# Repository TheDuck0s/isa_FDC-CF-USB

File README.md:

# ISA FDC, XT-CF, USB Card

This is an IBM XT-compatible FDC, XT-CF-Lite and USB card, based on a design (FDC & XT-CF-Lite-V4) by [Sergey Kiselev](https://github.com/skiselev).

# The Idea

The goal of this project is to create an XT-compatible computer on a passive backplane with a modular card-based architecture, minimizing the overall footprint while providing support for all common expansion cards.

# Hardware Documentation
Schematic PDF:
[Schematic - Version 1.0](isa_FDC-CF-USB_Schematic.pdf)

PCB PDF:
[Board Design - Version 1.0](isa_FDC-CF-USB_Board_Design.pdf)

Gerber Files:
[Gerber- Version 1.0](gerber/)

# Bill of Materials
    
coming soon...

# Release Notes

### Changes:

#### Version 1.0

 * Initial Release

 # Benchmarks

### Checkit 3.0 Benchmark:

#### @9.55 MHz
 * XT-CF: 725KB/s

# Final Note
 * The card is tested and works.
 * This card won't fit Sergey's case ([this one](https://github.com/skiselev/micro_8088_case)). The case will need to be enlarged.
 * Card size 185.3 mm x 102.9 mm

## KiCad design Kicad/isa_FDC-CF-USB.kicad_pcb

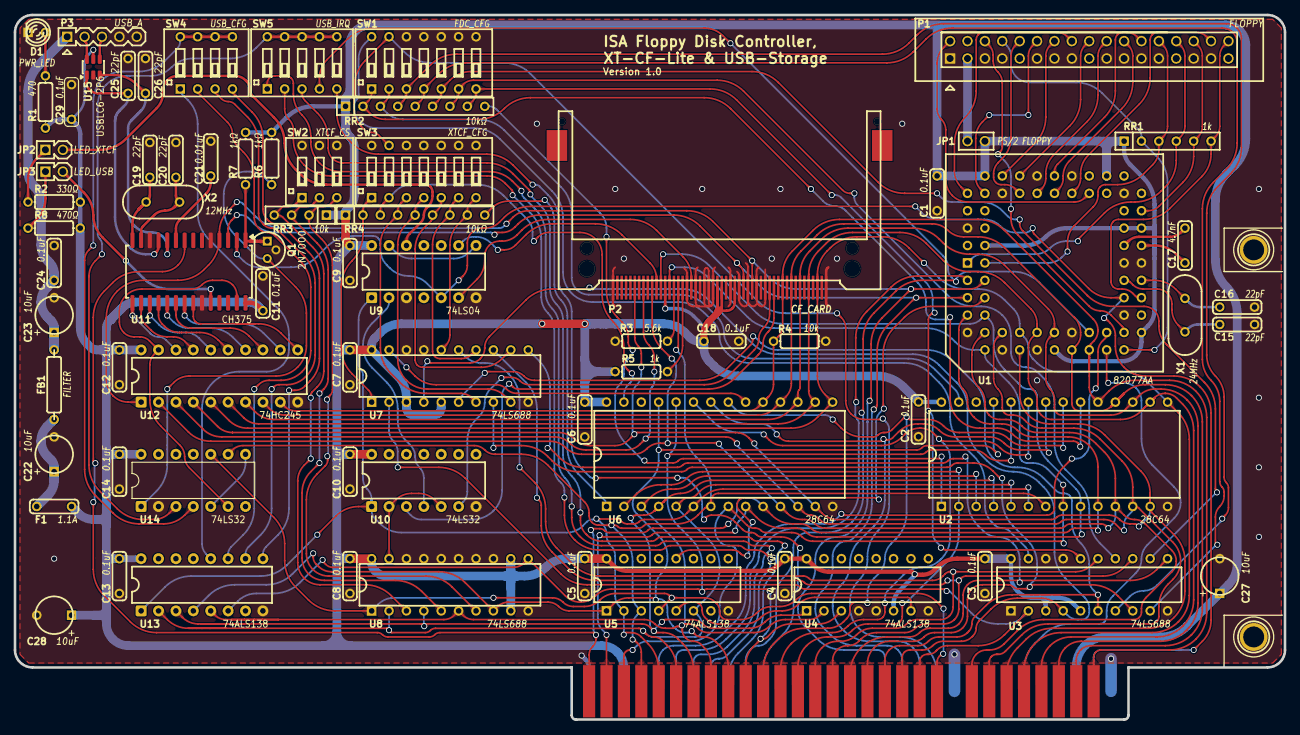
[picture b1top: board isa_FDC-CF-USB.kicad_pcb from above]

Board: 2 copper layers, 185.4 x 102.9 mm, 76 parts (0 on the bottom side), 130 nets.

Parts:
BUS1: PCB Edge Connector; Conn_Bus_ISA8
C1, C6, C7, C8, C9, C10, C11, C12, C13, C14, C18, C24, C29: 0.1uF; Cap_Cer_508
C2, C3, C4, C5: 0.1uF; Cap_Cer_504
C15, C16: 22pF; Cap_Cer_504
C17: 4.7nF; Cap_Cer_504
C19, C20, C25, C26: 22pF; Cap_Cer_508
C21: 0.01uF; Cap_Cer_508
C22, C23, C27, C28: 10uF; Cap_Tant_508
D1: PWR_LED; LED_3mm
F1: 1.1A; Cap_Cer_508
FB1: FILTER; Res_1016
HOLE1, HOLE2: CONN_1; HOLE_3MM
JP1: PS/2 FLOPPY; Conn_Pin_Header_2x1_Nokey
JP2: LED_XTCF; Conn_Pin_Header_2x1_2.54mm
JP3: LED_USB; Conn_Pin_Header_2x1_2.54mm
P1: FLOPPY; Conn_Pin_Header_17x2_2.54mm_Shrouded
P2: CF_CARD; Conn_CF_N7E50-Q516XX-40
P3: USB_A; Conn_Pin_Header_5x1_2.54mm
Q1: 2N7000; TO-92
R1: 470; Res_762
R2: 330Ω; Res_762
R3: 5.6k; Res_762
R4: 10k; Res_762
R5: 1k; Res_762
R6, R7: 1kΩ; Res_762
R8: 470Ω; Res_762
RR1: 1k; Conn_SIL6
RR2, RR4: 10kΩ; Conn_SIL9
RR3: 10k; Conn_SIL5
SW1: FDC_CFG; Switch_DIP_7_Positions
SW2: XTCF_CS; Switch_DIP_3_Positions
SW3: XTCF_CFG; Switch_DIP_7_Positions
SW4: USB_CFG; Switch_DIP_4_Positions
SW5: USB_IRQ; Switch_DIP_5_Positions
U1: 82077AA; PLCC68_TH
U2: 28C64; DIP28_600
U3: 74LS688; DIP20_300
U4, U5: 74ALS138; DIP16_300
U6: 28C64; IC_DIP28_600
U7, U8: 74LS688; IC_DIP20_300
U9: 74LS04; DIP-14_W7.62mm
U10, U14: 74LS32; DIP-14_W7.62mm
U11: CH375; SOP-28_8.4x18.16mm_P1.27mm
U12: 74HC245; DIP-20_W7.62mm
U13: 74ALS138; DIP-16_W7.62mm
U15: USBLC6-2P6; SOT-23-6
X1: 24MHz; Crystal_HC-49U_Vert
X2: 12MHz; Crystal_HC-49U_Vert

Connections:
/A0: BUS1.62 (SA0), U1.7 (A0), U2.10 (A0), U6.10 (A0), U11.8 (A0)
/A1: BUS1.61 (SA1), P2.20 (A0), U1.8 (A1), U2.9 (A1), U6.9 (A1)
/A2: BUS1.60 (SA2), P2.19 (A1), U1.10 (A2), U2.8 (A2), U6.8 (A2)
/A3: BUS1.59 (SA3), P2.18 (A2), U2.7 (A3), U5.3 (C), U6.7 (A3), U14.9
/A4: BUS1.58 (SA4), U2.6 (A4), U5.2 (B), U6.6 (A4), U9.1, U10.1, U13.1 (A)
/A5: BUS1.57 (SA5), U2.5 (A5), U5.6 (G1), U6.5 (A5), U8.2 (P0), U13.2 (B)
/A6: BUS1.56 (SA6), U2.4 (A6), U4.1 (A), U6.4 (A6), U8.4 (P1), U13.3 (C)
/A7: BUS1.55 (SA7), U2.3 (A7), U4.2 (B), U6.3 (A7), U8.6 (P2), U13.5 (~G2B)
/A8: BUS1.54 (SA8), U2.25 (A8), U5.1 (A), U6.25 (A8), U8.8 (P3), U13.4 (~G2A)
/A9: BUS1.53 (SA9), U2.24 (A9), U4.3 (C), U6.24 (A9), U8.11 (P4), U13.6 (G1)
/A10: BUS1.52 (SA10), U2.21 (A10), U6.21 (A10)
/A11: BUS1.51 (SA11), U2.23 (A11), U6.23 (A11)
/A12: BUS1.50 (SA12), U2.2 (A12), U6.2 (A12)
/A13: BUS1.49 (SA13), U3.15 (P6), U7.15 (P6)
/A14: BUS1.48 (SA14), U3.13 (P5), U7.13 (P5)
/A15: BUS1.47 (SA15), U3.11 (P4), U7.11 (P4)
/A16: BUS1.46 (SA16), U3.8 (P3), U7.8 (P3)
/A17: BUS1.45 (SA17), U3.6 (P2), U7.6 (P2)
/A18: BUS1.44 (SA18), U3.4 (P1), U7.4 (P1)
/A19: BUS1.43 (SA19), U3.2 (P0), U7.2 (P0)
/AEN: BUS1.42 (AEN), U5.4 (~G2A), U8.1 (~G), U14.10
/CF_DMARQ: P2.43 (~INPACK), R3.1
/CF_IORDY: P2.42 (IORDY), R5.1
/CF_RDY/~BUSY: RR4.9, U6.1 (RDY/~BUSY)
/D0: BUS1.40 (SD0), P2.21 (D0), U1.11 (DB0), U2.11 (DQ0), U6.11 (DQ0), U12.2 (A0)
/D1: BUS1.39 (SD1), P2.22 (D1), U1.13 (DB1), U2.12 (DQ1), U6.12 (DQ1), U12.3 (A1)
/D2: BUS1.38 (SD2), P2.23 (D2), U1.14 (DB2), U2.13 (DQ2), U6.13 (DQ2), U12.4 (A2)
/D3: BUS1.37 (SD3), P2.2 (D3), U1.15 (DB3), U2.15 (DQ3), U6.15 (DQ3), U12.5 (A3)
/D4: BUS1.36 (SD4), P2.3 (D4), U1.17 (DB4), U2.16 (DQ4), U6.16 (DQ4), U12.6 (A4)
/D5: BUS1.35 (SD5), P2.4 (D5), U1.19 (DB5), U2.17 (DQ5), U6.17 (DQ5), U12.7 (A5)
/D6: BUS1.34 (SD6), P2.5 (D6), U1.20 (DB6), U2.18 (DQ6), U6.18 (DQ6), U12.8 (A6)
/D7: BUS1.33 (SD7), P2.6 (D7), R4.1, U1.22 (DB7), U2.19 (DQ7), U6.19 (DQ7), U12.9 (A7)
/DENSL: P1.2, U1.49 (DENSEL)
/DIR: P1.18, U1.56 (DIR)
/DRQ2: BUS1.6 (DRQ2), U1.24 (DRQ)
/DSA: P1.14, U1.58 (DS0)
/DSB: P1.12, U1.62 (DS1)
/DSKCG: P1.34, RR1.6, U1.31 (DSKCHG)
/FDC_RDY/~BUSY: RR2.9, U2.1 (RDY/~BUSY)
/FLOPPY_VCC: JP1.2, P1.3
/HDSEL: P1.32, U1.51 (HDSEL)
/INDEX: P1.8, RR1.2, U1.26 (INDX)
/IRQ3: BUS1.25 (IRQ3), SW5.1
/IRQ4: BUS1.24 (IRQ4), SW5.2
/IRQ5: BUS1.23 (IRQ5), SW5.3
/IRQ6: BUS1.22 (IRQ6), SW5.4, U1.23 (INT)
/IRQ7: BUS1.21 (IRQ7), SW5.5
/MEA: P1.10, U1.57 (ME0)
/MEB: P1.16, U1.61 (ME1)
/RDATA: P1.30, RR1.5, U1.41 (RDDATA)
/RESETDRV: BUS1.2 (RESET), U1.32 (RESET), U9.5, U11.2 (RESET)
/STEP: P1.20, U1.55 (STEP)
/TC: BUS1.27 (TC), U1.25 (TC)
/TRK00: P1.26, RR1.3, U1.2 (TRK0)
/USB-D0: U11.15 (D0), U12.18 (B0)
/USB-D1: U11.16 (D1), U12.17 (B1)
/USB-D2: U11.17 (D2), U12.16 (B2)
/USB-D3: U11.18 (D3), U12.15 (B3)
/USB-D4: U11.19 (D4), U12.14 (B4)
/USB-D5: U11.20 (D5), U12.13 (B5)
/USB-D6: U11.21 (D6), U12.12 (B6)
/USB-D7: U11.22 (D7), U12.11 (B7)
/WDATA: P1.22, U1.53 (WRDATA)
/WE: P1.24, U1.52 (WE)
/WP: P1.28, RR1.4, U1.1 (WP)
/~ACT: JP3.2 (PM), U11.24 (~ACT)
/~CF_CS0: P2.7 (~CS0), U10.3
/~CF_CS1: P2.32 (~CS1), U10.6
/~CF_DASP: P2.45 (~DASP), U9.9
/~CF_RESET: P2.41 (~RESET), U9.6
/~CF_ROMW: RR4.3, SW3.2, U6.27 (~WE)
/~CF_ROM_CS: U6.20 (~CE), U7.19 (~P=Q)
/~DACK2: BUS1.26 (DACK2), U1.3 (~DACK)
/~FDC_CS: U1.6 (CS), U5.12 (~Y3)
/~FDC_ROMW: RR2.3, SW1.2, U2.27 (~WE)
/~FDC_ROM_CS: RR2.2, SW1.1, U2.20 (~CE)
/~IOR: BUS1.14 (IOR), P2.34 (~IORD), U1.4 (~RD), U11.4 (~RD), U12.1 (A->B)
/~IOW: BUS1.13 (IOW), P2.35 (~IOWR), U1.5 (~WR), U11.3 (~WR)
/~MEMR: BUS1.12 (MEMR), U2.22 (~OE), U6.22 (~OE)
/~MEMW: BUS1.11 (MEMW), SW1.13, SW3.13
/~ROM_CS_IN: SW1.14, U3.19 (~P=Q)
/~USB-CS: U11.27 (~CS), U12.19 (CE), U14.6
GND: BUS1.1 (GND), BUS1.10 (GND), BUS1.31 (GND), C1.2, C2.2, C3.2, C4.2, C5.2, C6.2, C7.2, C8.2, C9.2, C10.2, C11.1, C12.2, C13.2, C14.2, C15.2, C16.2, C18.2, C19.2, C20.2, C21.2, C22.2, C23.2, C24.2, C25.2, C26.2, C27.2, C28.2, C29.2, D1.1 (K), HOLE1.1 (1_1), HOLE2.1 (1_1), P1.1, P1.5, P1.7, P1.11, P1.13, P1.15, P1.19, P1.21, P1.23, P1.25, P1.29, P1.31, P2.1 (GND), P2.8 (A10), P2.9 (~ATASEL), P2.10 (A9), P2.11 (A8), P2.12 (A7), P2.14 (A6), P2.15 (A5), P2.16 (A4), P2.17 (A3), P2.39 (~CSEL), P2.50 (GND), P3.4 (GND), P3.5 (Shield), Q1.2 (S), R3.2, R4.2, SW1.8, SW1.9, SW1.10, SW1.11, SW1.12, SW2.4, SW2.5, SW2.6, SW3.8, SW3.9, SW3.10, SW3.11, SW3.12, SW3.14, U1.9 (GND), U1.12 (GND), U1.16 (GND), U1.21 (GND), U1.30 (DRV2), U1.35 (~INVERT), U1.36 (GND), U1.45 (AVSS), U1.50 (GND), U1.54 (GND), U1.59 (GND), U1.65 (GND), U2.14 (GND), U3.1 (~G), U3.10 (GND), U3.17 (P7), U3.18 (Q7), U4.4 (~G2A), U4.5 (~G2B), U4.8 (GND), U5.8 (GND), U6.14 (GND), U7.10 (GND), U7.17 (P7), U7.18 (Q7), U8.10 (GND), U8.13 (P5), U8.14 (Q5), U8.15 (P6), U8.16 (Q6), U8.17 (P7), U8.18 (Q7), U9.3, U9.7 (GND), U10.7 (GND), U11.5 (TXD), U11.12 (GND1), U11.23 (GND2), U12.10 (GND), U13.8 (GND), U14.2, U15.2 (GND)
unnamed: C22.1, F1.1, FB1.2
unnamed: D1.2 (A), R1.1
unnamed: JP2.1, R2.2
unnamed: JP2.2 (PM), U9.12
unnamed: JP3.1, R8.2
unnamed: P1.6, U1.28 (DRATE0)
unnamed: P3.3 (D+), U15.4 (I/O2)
unnamed: P3.2 (D-), U15.6 (I/O1)
unnamed: C23.1, C24.1, FB1.1, P3.1 (VBUS)
unnamed: Q1.3 (D), R6.2, U14.1
unnamed: Q1.1 (G), R7.1, U11.1 (~INT)
unnamed: SW4.5, SW4.6, SW4.7, SW4.8, U14.4
unnamed: SW5.6, SW5.7, SW5.8, SW5.9, SW5.10, U14.3
unnamed: C17.1, U1.38 (HIFIL)
unnamed: C17.2, U1.37 (LOFIL)
unnamed: C16.1, U1.33 (X1), X1.1
unnamed: C15.1, U1.34 (X2), X1.2
unnamed: RR2.4, SW1.3, U3.7 (Q2)
unnamed: RR2.5, SW1.4, U3.9 (Q3)
unnamed: RR2.6, SW1.5, U3.12 (Q4)
unnamed: RR2.7, SW1.6, U3.14 (Q5)
unnamed: RR2.8, SW1.7, U3.16 (Q6)
unnamed: U4.7 (~Y7), U5.5 (~G2B)
unnamed: RR4.4, SW3.3, U7.7 (Q2)
unnamed: RR4.5, SW3.4, U7.9 (Q3)
unnamed: RR4.6, SW3.5, U7.12 (Q4)
unnamed: RR4.7, SW3.6, U7.14 (Q5)
unnamed: RR4.8, SW3.7, U7.16 (Q6)
unnamed: RR4.2, SW3.1, U7.1 (~G)
unnamed: RR3.4, SW2.1, U8.3 (Q0)
unnamed: RR3.3, SW2.2, U8.5 (Q1)
unnamed: RR3.2, SW2.3, U8.7 (Q2)
unnamed: U8.19 (~P=Q), U10.2, U10.5
unnamed: U9.8, U9.13
unnamed: U9.2, U10.4
unnamed: U10.9, U10.10, U10.12, U10.13
unnamed: C21.1, U11.9 (U3)
unnamed: C26.1, U11.10 (UD+), U15.3 (I/O2)
unnamed: C25.1, U11.11 (UD-), U15.1 (I/O1)
unnamed: C19.1, U11.14 (X0), X2.1
unnamed: C20.1, U11.13 (X1), X2.2
unnamed: SW4.1, U13.12 (~Y3)
unnamed: SW4.2, U13.11 (~Y4)
unnamed: SW4.3, U13.10 (~Y5)
unnamed: SW4.4, U13.9 (~Y6)
unnamed: U14.5, U14.8
VCC: BUS1.3 (VCC), BUS1.29 (VCC), C1.1, C2.1, C3.1, C4.1, C5.1, C6.1, C7.1, C8.1, C9.1, C10.1, C11.2, C12.1, C13.1, C14.1, C18.1, C27.1, C28.1, C29.1, F1.2, JP1.1, P2.13 (VCC), P2.36 (~WE), P2.38 (VCC), P2.44 (~REG), R1.2, R2.1, R5.2, R6.1, R7.2, R8.1, RR1.1 (COM), RR2.1 (COM), RR3.1 (COM), RR4.1 (COM), U1.18 (VCC), U1.27 (IDENT), U1.39 (PLL0), U1.40 (VCC), U1.46 (AVCC), U1.60 (VCC), U1.68 (VCC), U2.28 (VCC), U3.3 (Q0), U3.5 (Q1), U3.20 (VCC), U4.6 (G1), U4.16 (VCC), U5.16 (VCC), U6.28 (VCC), U7.3 (Q0), U7.5 (Q1), U7.20 (VCC), U8.9 (Q3), U8.12 (Q4), U8.20 (VCC), U9.14 (VCC), U10.14 (VCC), U11.28 (VCC), U12.20 (VCC), U13.16 (VCC), U15.5 (VBUS)
